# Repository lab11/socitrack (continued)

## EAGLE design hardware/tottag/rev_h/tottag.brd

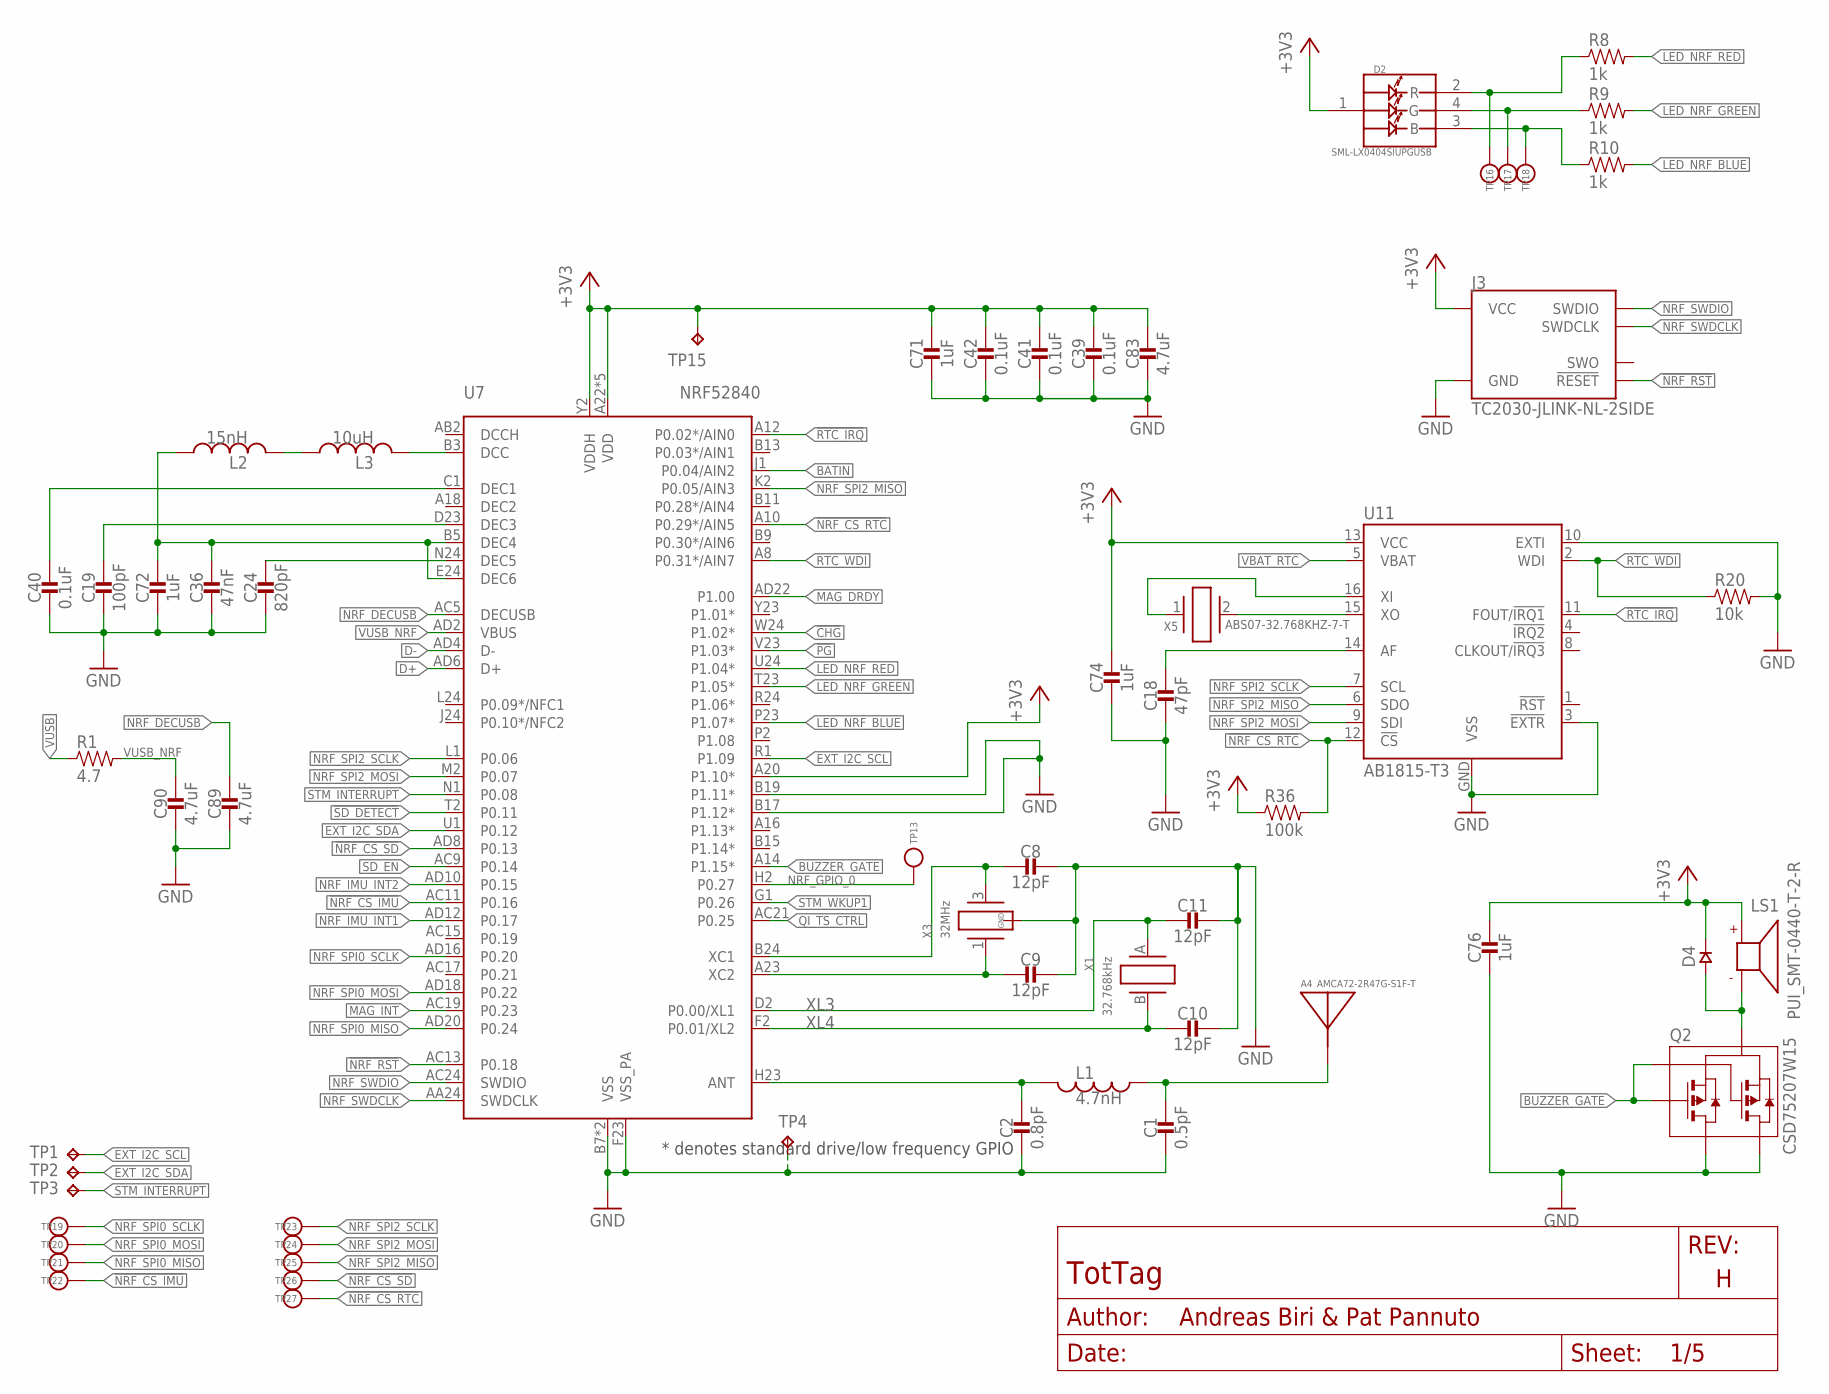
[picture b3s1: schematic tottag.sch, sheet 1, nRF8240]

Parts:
A4: AMCA72-2R47G-S1F-T; AMCA72-2R470G-S1F-T
C1: 0.5pF; 0402_CAP; MPN GJM1555C1HR50WB01D; DIGIKEY 490-11250-1-ND
C2: 0.8pF; 0402_CAP; MPN GJM1555C1HR80WB01D; DIGIKEY 490-11253-1-ND
C8, C9, C10, C11: 12pF; 0402_CAP; MPN CBR04C120F5GAC; DIGIKEY 399-8815-2-ND
C18: 47pF; 0402_CAP; MPN GRM1555C1H470JA01D; DIGIKEY 490-5942-1-ND
C19: 100pF; 0402_CAP; MPN GRM1555C1H101JA01D; DIGIKEY 490-5922-1-ND
C24: 820pF; 0402_CAP; MPN C0402C821J5GACTU; DIGIKEY 399-11129-2-ND
C36: 47nF; 0402_CAP; MPN C1005X7R1C473K050BC; DIGIKEY 445-1264-1-ND
C39, C40, C41: 0.1uF; 0402_CAP; MPN GRM155R71C104KA88J; DIGIKEY 490-6328-1-ND
C42: 0.1uF; 0402_CAP
C71: 1uF; 0402_CAP
C72, C74, C76: 1uF; 0402_CAP; MPN GRM155R70G105KA12D; DIGIKEY 490-7195-1-ND
C83: 4.7uF; 0402_CAP
C89, C90: 4.7uF; 0402_CAP; MPN C1005X5R0J475K050BC; DIGIKEY 445-5947-1-ND
D2: SML-LX0404SIUPGUSB; 1MM_SQ_4PAD
D4: DIODE0402; 0402_DIODE; MPN CDSQR400B-HF; DIGIKEY 641-2087-1-ND
J3: TC2030-JLINK-NL-2SIDE; TC2030-IDC-NL-2SIDE
L1: 4.7nH; 0402_CAP; MPN LQW15AN4N7G8ZD; DIGIKEY 490-15482-1-ND
L2: 15nH; 0402_CAP; MPN HK100515NJ-T; DIGIKEY 587-1521-1-ND
L3: 10uH; 0603_CAP; MPN LQM18FN100M00D; DIGIKEY 490-4025-1-ND
LS1: PUI_SMT-0440-T-2-R; SMT-0440-T-2-R
Q2: CSD75207W15; DSBGA
R1: 4.7; 0402_RES; MPN RMCF0402FT4R70; DIGIKEY RMCF0402FT4R70CT-ND
R8: 1k; 0402_RES; MPN RMCF0402FT1K00; DIGIKEY RMCF0402FT1K00CT-ND
R9, R10: 1k; 0402_RES
R20: 10k; 0402_RES; MPN RC0402JR-0710KL; DIGIKEY 311-10KJRCT-ND
R36: 100k; 0402_RES
TP1, TP2, TP3, TP4, TP15: TPTP06SQ; TP06SQ
TP13, TP16, TP17, TP18, TP19, TP20, TP21, TP22, TP23, TP24, TP25, TP26, TP27: TEST-POINT; PAD.03X.03
U7: NRF52840; AQFN73
U11: AB1815-T3; QFN-16-3MM
X1: 32.768kHz; ABS05
X3: 32MHz; TXC-7V
X5: ABS07-32.768KHZ-7-T; ABS07

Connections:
!CHG: U7.W24 (P1.02*); also elsewhere on the board
!NRF_CS_IMU: TP22.P$1, U7.AC11 (P0.16); also elsewhere on the board
!NRF_CS_RTC: R36.2, TP27.P$1, U7.A10 (P0.29*/AIN5), U11.12 (!CS)
!NRF_CS_SD: TP26.P$1, U7.AD8 (P0.13); also elsewhere on the board
!NRF_RST: J3.3 (!RESET), J3.B3 (!RESET), U7.AC13 (P0.18)
!PG: U7.V23 (P1.03*); also elsewhere on the board
!RTC_IRQ: U7.A12 (P0.02*/AIN0), U11.11 (FOUT/!IRQ1)
!SD_DETECT: U7.T2 (P0.11); also elsewhere on the board
+3V3: C39.1, C41.1, C42.1, C71.1, C74.1, C76.1, C83.1, D2.1 (VDD), D4.CATHODE, J3.1 (VCC), J3.B1 (VCC), LS1.+, R36.1, TP15.TP, U7.A20 (P1.10*), U7.A22 (VDD), U7.AD14 (VDD), U7.AD23 (VDD), U7.B1 (VDD), U7.W1 (VDD), U7.Y2 (VDDH), U11.13 (VCC); also elsewhere on the board
BATIN: U7.J1 (P0.04/AIN2); also elsewhere on the board
BLE_ANT: A4.S1, C1.1, L1.1
BUZZER_GATE: Q2.A1 (G1), Q2.C1 (G2), U7.A14 (P1.15*)
D+: U7.AD6 (D+); also elsewhere on the board
D-: U7.AD4 (D-); also elsewhere on the board
EXT_I2C_SCL: TP1.TP, U7.R1 (P1.09); also elsewhere on the board
EXT_I2C_SDA: TP2.TP, U7.U1 (P0.12); also elsewhere on the board
GND: C1.2, C2.2, C8.1, C9.1, C10.1, C11.1, C18.2, C19.2, C24.2, C36.2, C39.2, C40.2, C41.2, C42.2, C71.2, C72.2, C74.2, C76.2, C83.2, C89.2, C90.2, J3.5 (GND), J3.B5 (GND), Q2.A2 (D1), Q2.A3 (D1), Q2.B2 (D2), Q2.B3 (D1), Q2.C2 (D2), Q2.C3 (D2), R20.2, TP4.TP, U7.B7 (VSS), U7.B17 (P1.12*), U7.B19 (P1.11*), U7.F23 (VSS_PA), U7.GND (VSS), U11.3 (!EXTR), U11.10 (EXTI), U11.GND (VSS), X3.2 (GND), X3.4 (GND); also elsewhere on the board
LED_NRF_BLUE: R10.2, U7.P23 (P1.07*)
LED_NRF_BLUE_COMM: D2.3 (B), R10.1, TP18.P$1
LED_NRF_GREEN: R9.2, U7.T23 (P1.05*)
LED_NRF_GREEN_COMM: D2.4 (G), R9.1, TP17.P$1
LED_NRF_RED: R8.2, U7.U24 (P1.04*)
LED_NRF_RED_COMM: D2.2 (R), R8.1, TP16.P$1
MAG_DRDY: U7.AD22 (P1.00); also elsewhere on the board
MAG_INT: U7.AC19 (P0.23); also elsewhere on the board
unnamed: D4.ANODE, LS1.- (N), Q2.B1 (S)
unnamed: C2.1, L1.2, U7.H23 (ANT)
unnamed: C8.2, U7.B24 (XC1), X3.3 (2)
unnamed: C9.2, U7.A23 (XC2), X3.1
unnamed: C18.1, U11.14 (AF)
unnamed: L2.2, L3.1
unnamed: U11.16 (XI), X5.1
unnamed: U11.15 (XO), X5.2
NRF_DCC: L3.2, U7.B3 (DCC)
NRF_DECAP1: C40.1, U7.C1 (DEC1)
NRF_DECAP3: C19.1, U7.D23 (DEC3)
NRF_DECAP5: C24.1, U7.N24 (DEC5)
NRF_DECAP46: C36.1, C72.1, L2.1, U7.B5 (DEC4), U7.E24 (DEC6)
NRF_DECUSB: C89.1, U7.AC5 (DECUSB)
NRF_GPIO_0: TP13.P$1, U7.H2 (P0.27)
NRF_IMU_INT1: U7.AD12 (P0.17); also elsewhere on the board
NRF_IMU_INT2: U7.AD10 (P0.15); also elsewhere on the board
NRF_SPI0_MISO: TP21.P$1, U7.AD20 (P0.24); also elsewhere on the board
NRF_SPI0_MOSI: TP20.P$1, U7.AD18 (P0.22); also elsewhere on the board
NRF_SPI0_SCLK: TP19.P$1, U7.AD16 (P0.20); also elsewhere on the board
NRF_SPI2_MISO: TP25.P$1, U7.K2 (P0.05/AIN3), U11.6 (SDO); also elsewhere on the board
NRF_SPI2_MOSI: TP24.P$1, U7.M2 (P0.07), U11.9 (SDI); also elsewhere on the board
NRF_SPI2_SCLK: TP23.P$1, U7.L1 (P0.06), U11.7 (SCL); also elsewhere on the board
NRF_SWDCLK: J3.4 (SWDCLK), J3.B4 (SWDCLK), U7.AA24 (SWDCLK)
NRF_SWDIO: J3.2 (SWDIO), J3.B2 (SWDIO), U7.AC24 (SWDIO)
QI_TS_CTRL: U7.AC21 (P0.25); also elsewhere on the board
RTC_WDI: R20.1, U7.A8 (P0.31*/AIN7), U11.2 (WDI)
SD_EN: U7.AC9 (P0.14); also elsewhere on the board
STM_INTERRUPT: TP3.TP, U7.N1 (P0.08); also elsewhere on the board
STM_WKUP1: U7.G1 (P0.26); also elsewhere on the board
VBAT_RTC: U11.5 (VBAT); also elsewhere on the board
VUSB: R1.1; also elsewhere on the board
VUSB_NRF: C90.1, R1.2, U7.AD2 (VBUS)
XL3: C11.2, U7.D2 (P0.00/XL1), X1.A (1)
XL4: C10.2, U7.F2 (P0.01/XL2), X1.B (2)

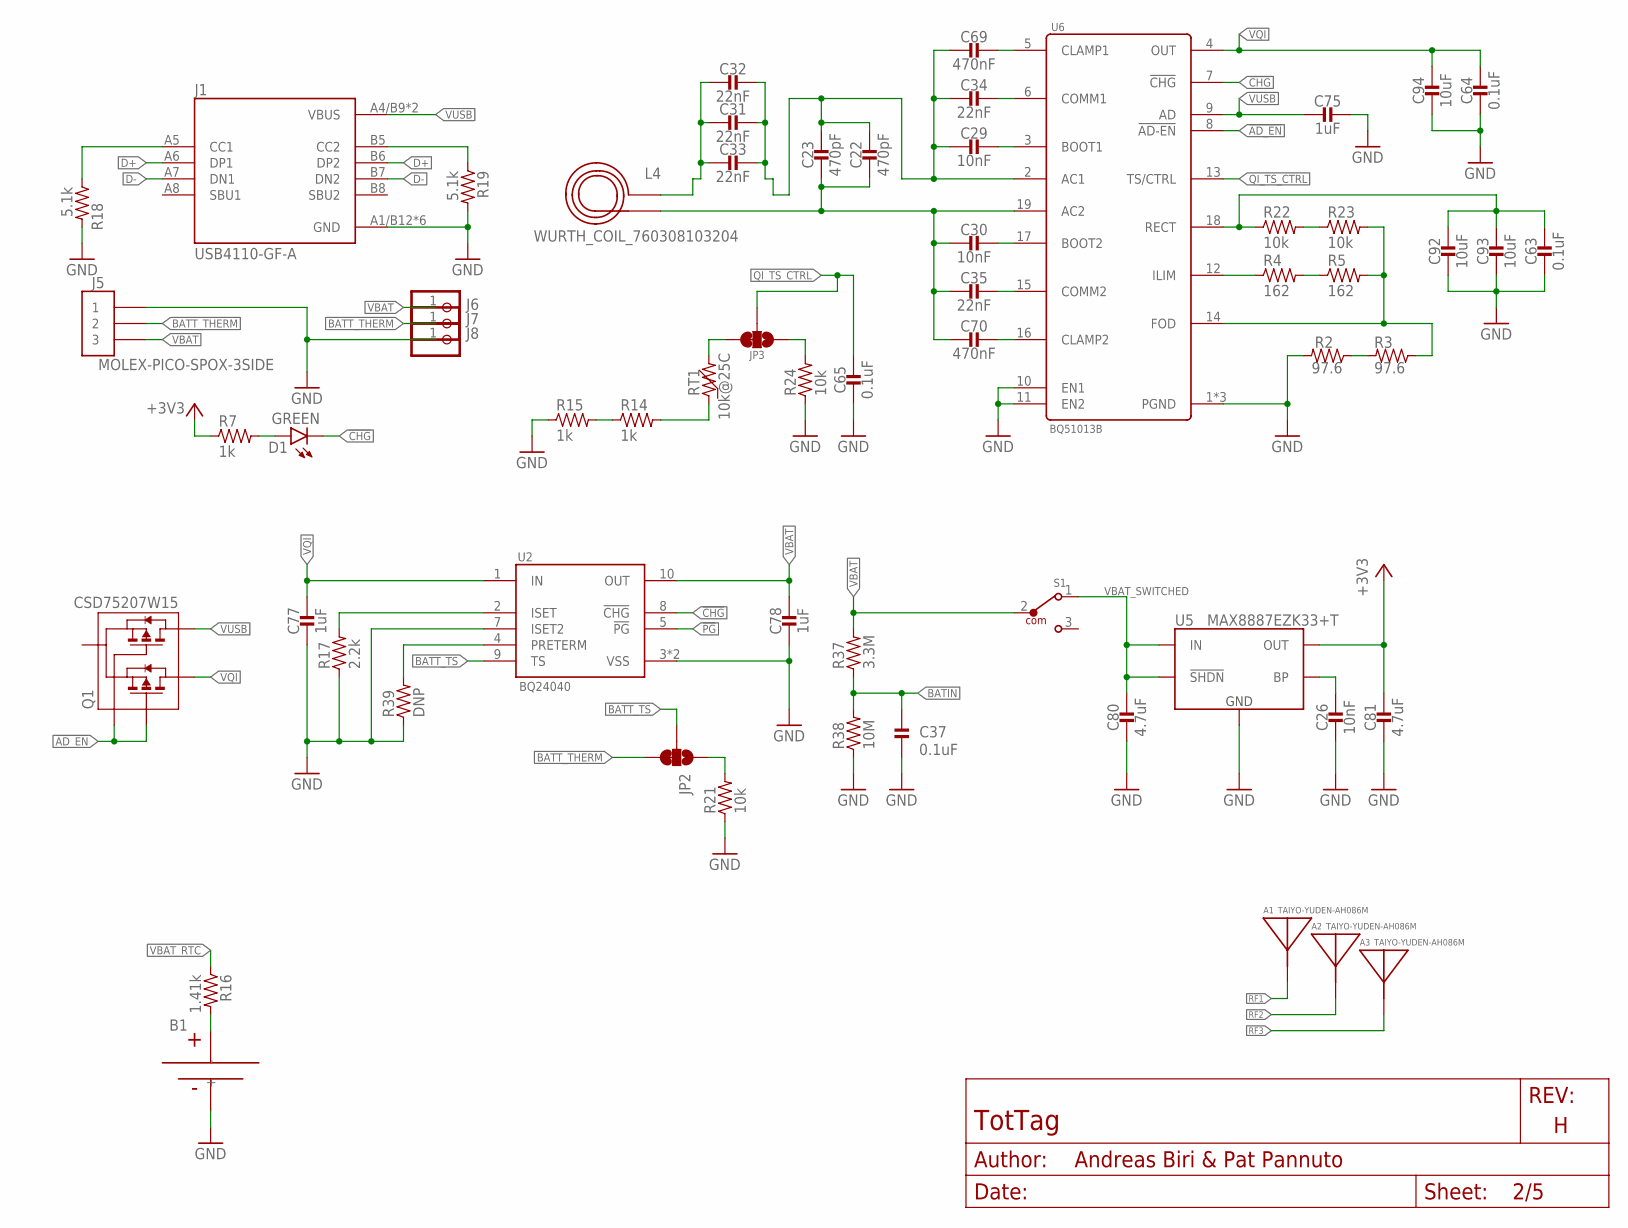
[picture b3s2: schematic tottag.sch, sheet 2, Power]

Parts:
A1, A2, A3: TAIYO-YUDEN-AH086M
B1: MS518SE; MS518SE-FL35E
C22, C23: 470pF; 0402_CAP; MPN GRM1555C1H471JA01J; DIGIKEY 490-6242-1-ND
C26: 10nF; 0402_CAP
C29, C30: 10nF; 0402_CAP; MPN GRM155R71H103KA88J; DIGIKEY 490-6351-2-ND
C31, C32, C33: 22nF; 0402_CAP; MPN GRM155R71E223JA61D; DIGIKEY 490-10699-2-ND
C34, C35: 22nF; 0402_CAP; MPN CC0402ZRY5V8BB223; DIGIKEY 311-3823-1-ND
C37: 0.1uF; 0402_CAP
C63, C64, C65: 0.1uF; 0402_CAP; MPN GRM155R71C104KA88J; DIGIKEY 490-6328-1-ND
C69, C70: 470nF; 0402_CAP; MPN GRT155R61E474ME01D; DIGIKEY 490-12270-1-ND
C75: 1uF; 0402_CAP
C77, C78: 1uF; 0402_CAP; MPN GRM155R70G105KA12D; DIGIKEY 490-7195-1-ND
C80, C81: 4.7uF; 0402_CAP
C92, C93, C94: 10uF; 0603_CAP; MPN CM105X5R106M25AT; DIGIKEY 1253-CM105X5R106M25ATCT-ND
D1: GREEN; LED-0603; MPN LTST-C191KGKT; DIGIKEY 160-1446-1-ND
J1: USB4110-GF-A; GCT_USB4110-GF-A
J5: MOLEX-PICO-SPOX-3SIDE; MOLEX-PICO-SPOX-3_SIDE
J6, J7, J8: PINHD-1X1; 1X01
JP2, JP3: JUMPER-SMT_3_1-NC_TRACE_SILK; SMT-JUMPER_3_1-NC_TRACE_SILK
L4: WURTH_COIL_760308103204
Q1: CSD75207W15; DSBGA
R2, R3: 97.6; 0402_RES; MPN RMCF0402FT97R6; DIGIKEY RMCF0402FT97R6CT-ND
R4, R5: 162; 0402_RES; MPN RMCF0402FT162R; DIGIKEY RMCF0402FT162RCT-ND
R7, R14, R15: 1k; 0402_RES
R16: 1.41k; 0402_RES; MPN RMCF0402FT1K40; DIGIKEY RMCF0402FT1K40CT-ND
R17: 2.2k; 0402_RES; MPN RMCF0402JT2K20; DIGIKEY RMCF0402JT2K20CT-ND
R18, R19: 5.1k; 0402_RES; MPN RMCF0402FT5K10; DIGIKEY RMCF0402FT5K10CT-ND
R21, R22, R23, R24: 10k; 0402_RES; MPN RC0402JR-0710KL; DIGIKEY 311-10KJRCT-ND
R37: 3.3M; 0402_RES; MPN RMCF0402FT3M30; DIGIKEY RMCF0402FT3M30CT-ND
R38: 10M; 0402_RES; MPN RMCF0402FT10M0; DIGIKEY RMCF0402FT10M0CT-ND
R39: DNP; 0402_RES
RT1: 10k@25C; 0402_RES; MPN NCU15XH103F60RC; DIGIKEY 490-18149-1-ND
S1: 450404015514; DIGIKEY 732-13665-1-ND
U2: BQ24040; DSQ0010A
U5: MAX8887EZK33+T; SOT-23-5
U6: BQ51013B; RHL0020A

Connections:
!AD_EN: Q1.A1 (G1), Q1.C1 (G2), U6.8 (!AD-EN)
!CHG: D1.C, U2.8 (!CHG), U6.7 (!CHG); also elsewhere on the board
!PG: U2.5 (!PG); also elsewhere on the board
+3V3: C81.1, R7.1, U5.5 (OUT); also elsewhere on the board
BATIN: C37.2, R37.1, R38.2; also elsewhere on the board
BATT_THERM: J5.2, J5.2SUPP (2), J7.1, JP2.3
BATT_TS: JP2.2, U2.9 (TS)
BQ_AC1: C22.1, C23.1, C29.2, C31.1, C32.1, C33.1, C34.2, C69.2, U6.2 (AC1)
BQ_AC2: C22.2, C23.2, C30.2, C35.2, C70.2, L4.P$2 (2), U6.19 (AC2)
BQ_BOOT1: C29.1, U6.3 (BOOT1)
BQ_BOOT2: C30.1, U6.17 (BOOT2)
BQ_CLAMP1: C69.1, U6.5 (CLAMP1)
BQ_CLAMP2: C70.1, U6.16 (CLAMP2)
BQ_COMM1: C34.1, U6.6 (COMM1)
BQ_COMM2: C35.1, U6.15 (COMM2)
BQ_FOD: R3.1, R5.2, R23.2, U6.14 (FOD)
BQ_ILM: R4.1, U6.12 (ILIM)
BQ_RECT: C63.1, C92.1, C93.1, R22.1, U6.18 (RECT)
COIL_AC1: C31.2, C32.2, C33.2, L4.P$1 (1)
D+: J1.A6 (DP1), J1.B6 (DP2); also elsewhere on the board
D-: J1.A7 (DN1), J1.B7 (DN2); also elsewhere on the board
GND: B1.-, C26.2, C37.1, C63.2, C64.2, C65.2, C75.1, C77.2, C78.2, C80.2, C81.2, C92.2, C93.2, C94.2, J1.A1/B12 (GND), J1.B1/A12 (GND), J1.S1 (GND), J1.S2 (GND), J1.S3 (GND), J1.S4 (GND), J5.1, J5.1SUPP (1), J8.1, R2.2, R15.1, R17.1, R18.2, R19.2, R21.1, R24.1, R38.1, R39.1, U2.3 (VSS), U2.7 (ISET2), U2.PAD (VSS), U5.2 (GND), U6.1 (PGND), U6.10 (EN1), U6.11 (EN2), U6.20 (PGND), U6.PAD (PGND); also elsewhere on the board
unnamed: J1.B5 (CC2), R19.1
unnamed: C26.1, U5.4 (BP)
unnamed: J1.A5 (CC1), R18.1
unnamed: R2.1, R3.2
unnamed: R17.2, U2.2 (ISET)
unnamed: B1.+, R16.2
unnamed: JP2.1, R21.2
unnamed: R39.2, U2.4 (PRETERM)
unnamed: D1.A, R7.2
unnamed: R22.2, R23.1
unnamed: R4.2, R5.1
unnamed: JP3.1, R24.2
unnamed: JP3.3, RT1.2
unnamed: R14.2, RT1.1
unnamed: R14.1, R15.2
QI_TS_CTRL: C65.1, JP3.2, U6.13 (TS/CTRL); also elsewhere on the board
RF1: A1.A; also elsewhere on the board
RF2: A2.A; also elsewhere on the board
RF3: A3.A; also elsewhere on the board
VBAT: C78.1, J5.3, J5.3SUPP (3), J6.1, R37.2, S1.2, U2.10 (OUT)
VBAT_RTC: R16.1; also elsewhere on the board
VBAT_SWITCHED: C80.1, S1.1, U5.1 (IN), U5.3 (!SHDN)
VQI: C64.1, C77.1, C94.1, Q1.A2 (D1), Q1.A3 (D1), Q1.B3 (D1), U2.1 (IN), U6.4 (OUT)
VUSB: C75.2, J1.A4/B9 (VBUS), J1.B4/A9 (VBUS), Q1.B2 (D2), Q1.C2 (D2), Q1.C3 (D2), U6.9 (AD); also elsewhere on the board

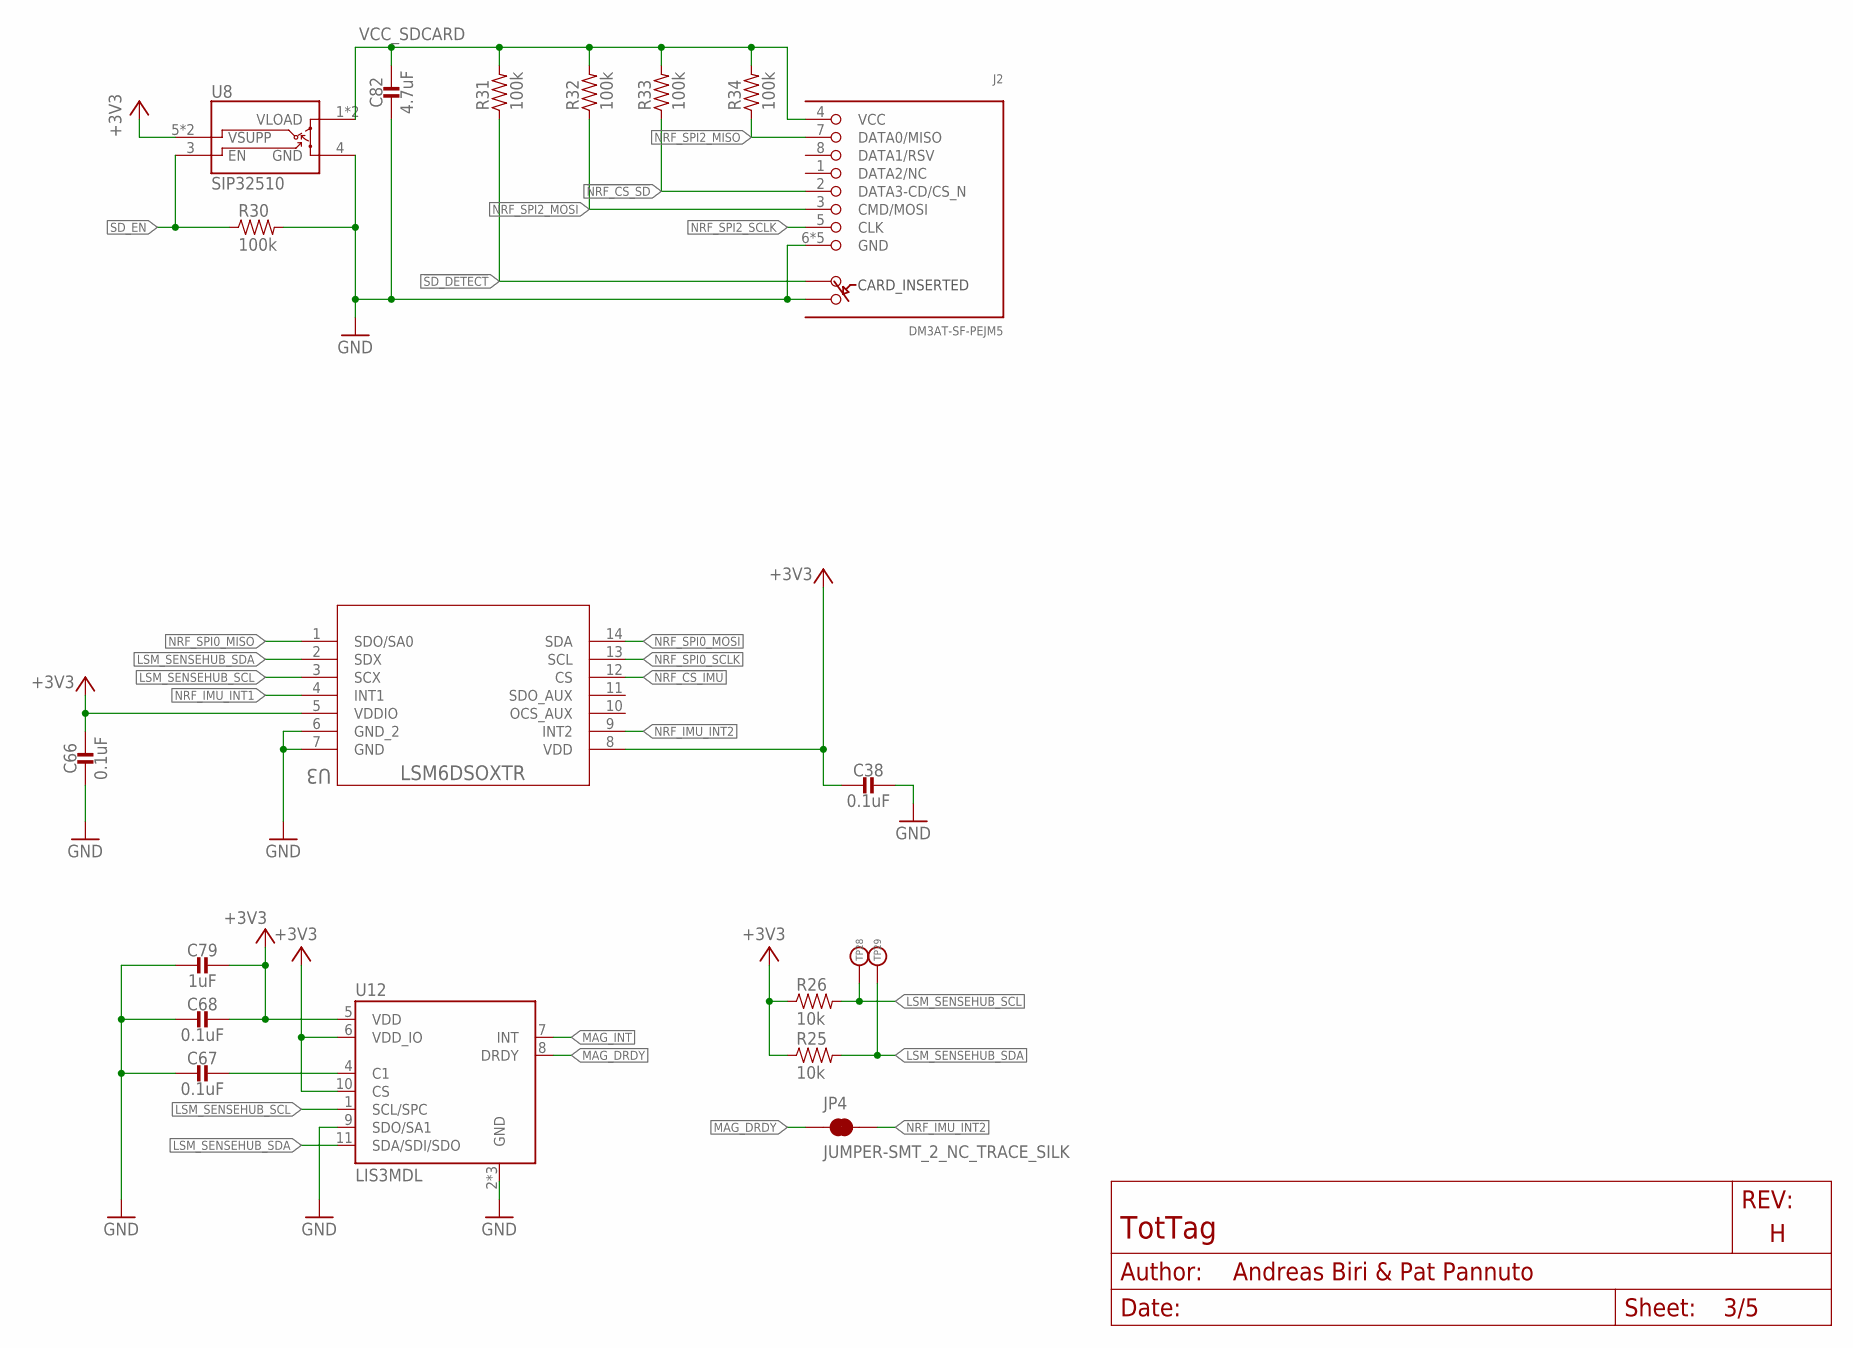
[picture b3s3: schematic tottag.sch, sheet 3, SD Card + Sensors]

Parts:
C38, C66, C67, C68: 0.1uF; 0402_CAP; MPN GRM155R71C104KA88J; DIGIKEY 490-6328-1-ND
C79: 1uF; 0402_CAP; MPN GRM155R70G105KA12D; DIGIKEY 490-7195-1-ND
C82: 4.7uF; 0402_CAP; MPN C1005X5R0J475K050BC; DIGIKEY 445-5947-1-ND
J2: DM3AT-SF-PEJM5
JP4: JUMPER-SMT_2_NC_TRACE_SILK; SMT-JUMPER_2_NC_TRACE_SILK
R25, R26: 10k; 0402_RES; MPN RC0402JR-0710KL; DIGIKEY 311-10KJRCT-ND
R30, R31, R32, R33, R34: 100k; 0402_RES
TP28, TP29: TEST-POINT; PAD.03X.03
U3: LSM6DSOXTR; LGA-14L_STM
U8: SIP32510; TSOT23-6
U12: LIS3MDL; LGA-12

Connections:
!NRF_CS_IMU: U3.12 (CS); also elsewhere on the board
!NRF_CS_SD: J2.2 (DATA3-CD/CS_N), R33.1; also elsewhere on the board
!SD_DETECT: J2.A, R31.1; also elsewhere on the board
+3V3: C38.2, C66.1, C68.1, C79.1, R25.1, R26.1, U3.5 (VDDIO), U3.8 (VDD), U8.5 (VSUPP), U8.6 (VSUPP), U12.5 (VDD), U12.6 (VDD_IO), U12.10 (CS); also elsewhere on the board
GND: C38.1, C66.2, C67.2, C68.2, C79.2, C82.2, J2.6 (GND), J2.B, J2.MOUNT0 (GND), J2.MOUNT1 (GND), J2.MOUNT2 (GND), J2.MOUNT3 (GND), R30.2, U3.6 (GND_2), U3.7 (GND), U8.4 (GND), U12.2 (GND), U12.3 (GND), U12.9 (SDO/SA1), U12.12 (GND); also elsewhere on the board
LSM_SENSEHUB_SCL: R26.2, TP28.P$1, U3.3 (SCX), U12.1 (SCL/SPC)
LSM_SENSEHUB_SDA: R25.2, TP29.P$1, U3.2 (SDX), U12.11 (SDA/SDI/SDO)
MAG_DRDY: JP4.1, U12.8 (DRDY); also elsewhere on the board
MAG_INT: U12.7 (INT); also elsewhere on the board
unnamed: C67.1, U12.4 (C1)
NRF_IMU_INT1: U3.4 (INT1); also elsewhere on the board
NRF_IMU_INT2: JP4.2, U3.9 (INT2); also elsewhere on the board
NRF_SPI0_MISO: U3.1 (SDO/SA0); also elsewhere on the board
NRF_SPI0_MOSI: U3.14 (SDA); also elsewhere on the board
NRF_SPI0_SCLK: U3.13 (SCL); also elsewhere on the board
NRF_SPI2_MISO: J2.7 (DATA0/MISO), R34.1; also elsewhere on the board
NRF_SPI2_MOSI: J2.3 (CMD/MOSI), R32.1; also elsewhere on the board
NRF_SPI2_SCLK: J2.5 (CLK); also elsewhere on the board
SD_EN: R30.1, U8.3 (EN); also elsewhere on the board
VCC_SDCARD: C82.1, J2.4 (VCC), R31.2, R32.2, R33.2, R34.2, U8.1 (VLOAD), U8.2 (VLOAD)

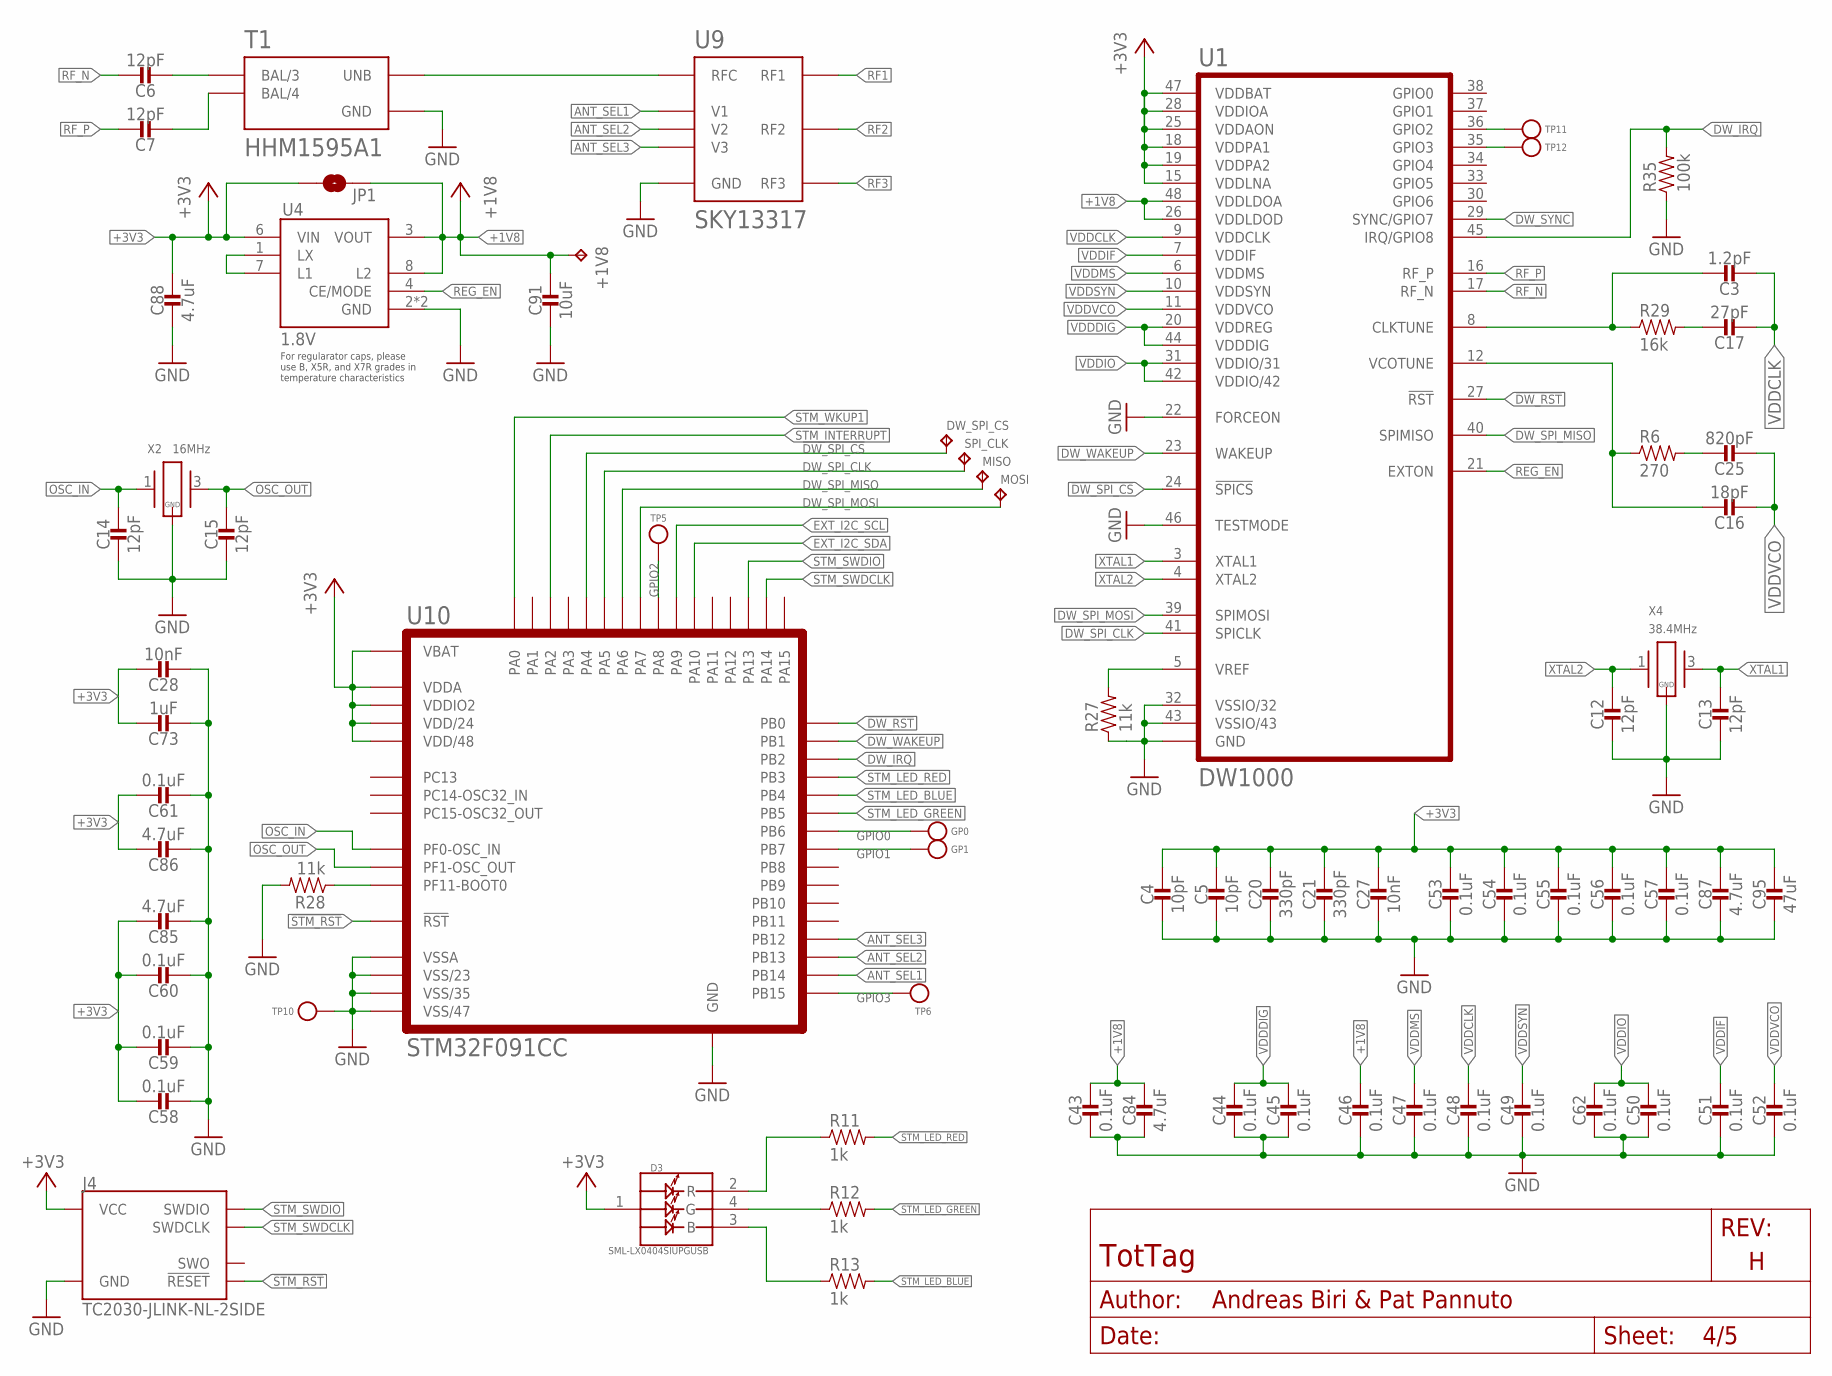
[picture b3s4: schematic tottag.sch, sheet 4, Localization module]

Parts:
+1V8: TPTP06SQ; TP06SQ
C3: 1.2pF; 0402_CAP; MPN GJM1555C1H1R2CB01D; DIGIKEY 490-3085-1-ND
C4, C5: 10pF; 0402_CAP; MPN 885012005074; DIGIKEY 732-12054-1-ND
C6, C7: 12pF; 0201_CAP; MPN CBR02C120F3GAC; DIGIKEY 399-8604-2-ND
C12, C13, C14, C15: 12pF; 0402_CAP; MPN CBR04C120F5GAC; DIGIKEY 399-8815-2-ND
C16: 18pF; 0402_CAP; MPN CBR04C180F5GAC; DIGIKEY 399-8828-1-ND
C17: 27pF; 0402_CAP; MPN GJM1555C1H270FB01D; DIGIKEY 490-16380-1-ND
C20, C21: 330pF; 0402_CAP; MPN CC0402JRX7R9BB331; DIGIKEY 311-3768-1-ND
C25: 820pF; 0402_CAP; MPN C0402C821J5GACTU; DIGIKEY 399-11129-2-ND
C27, C28: 10nF; 0402_CAP
C43, C44, C45, C46, C47, C48, C49, C50, C51, C52, C53, C54, C55, C56, C57, C58, C59, C60, C61, C62: 0.1uF; 0402_CAP
C73: 1uF; 0402_CAP
C84, C85, C86, C87, C88: 4.7uF; 0402_CAP
C91: 10uF; 0603_CAP; MPN CM105X5R106M25AT; DIGIKEY 1253-CM105X5R106M25ATCT-ND
C95: 47uF; 0603_CAP; MPN GRM188R60J476ME15D; DIGIKEY 490-13247-1-ND
D3: SML-LX0404SIUPGUSB; 1MM_SQ_4PAD
DW_SPI_CS: TPTP06SQ; TP06SQ
GP0, GP1: TEST-POINT; PAD.03X.03
J4: TC2030-JLINK-NL-2SIDE; TC2030-IDC-NL-2SIDE
JP1: JUMPER-SMT_2_NO_SILK; SMT-JUMPER_2_NO_SILK
MISO: TPTP06SQ; TP06SQ
MOSI: TPTP06SQ; TP06SQ
R6: 270; 0402_RES; MPN RMCF0402FT270R; DIGIKEY RMCF0402FT270RCT-ND
R11, R12, R13: 1k; 0402_RES
R27, R28: 11k; 0402_RES; MPN RMCF0402FT11K0; DIGIKEY RMCF0402FT11K0CT-ND
R29: 16k; 0402_RES; MPN RMCF0402FT16K0; DIGIKEY RMCF0402FT16K0CT-ND
R35: 100k; 0402_RES
SPI_CLK: TPTP06SQ; TP06SQ
T1: HHM1595A1; EIA-0805
TP5, TP6, TP10, TP11, TP12: TEST-POINT; PAD.03X.03
U1: DW1000; QFN-48-DW1000
U4: 1.8V; XCL20X
U9: SKY13317; MLPQ-UT-8
U10: STM32F091CC; UFQFPN-48
X2: 16MHz; FA-20H; MPN FA-20H 16.0000MF10Z-AJ3; DIGIKEY SER3913CT-ND
X4: 38.4MHz; FA-20H; MPN FA-20H 38.4000MF10Z-AS3; DIGIKEY SER3631CT-ND

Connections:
!DW_RST: U1.27 (!RST), U10.18 (PB0)
!DW_SPI_CS: DW_SPI_CS.TP, U1.24 (!SPICS), U10.14 (PA4)
!STM_RST: J4.3 (!RESET), J4.B3 (!RESET), U10.7 (!RST)
+1V8: +1V8.TP, C43.1, C46.1, C84.1, C91.1, JP1.2, U1.26 (VDDLDOD), U1.48 (VDDLDOA), U4.3 (VOUT), U4.8 (L2)
+3V3: C4.1, C5.1, C20.1, C21.1, C27.1, C28.1, C53.1, C54.1, C55.1, C56.1, C57.1, C58.1, C59.1, C60.1, C61.1, C73.1, C85.1, C86.1, C87.1, C88.1, C95.1, D3.1 (VDD), J4.1 (VCC), J4.B1 (VCC), JP1.1, U1.15 (VDDLNA), U1.18 (VDDPA1), U1.19 (VDDPA2), U1.25 (VDDAON), U1.28 (VDDIOA), U1.47 (VDDBAT), U4.6 (VIN), U10.1 (VBAT), U10.9 (VDDA), U10.24 (VDD/24), U10.36 (VDDIO2), U10.48 (VDD/48); also elsewhere on the board
ANT_SEL1: U9.3 (V1), U10.27 (PB14)
ANT_SEL2: U9.6 (V2), U10.26 (PB13)
ANT_SEL3: U9.7 (V3), U10.25 (PB12)
DW_IRQ: R35.2, U1.45 (IRQ/GPIO8), U10.20 (PB2)
DW_SPI_CLK: SPI_CLK.TP, U1.41 (SPICLK), U10.15 (PA5)
DW_SPI_MISO: MISO.TP, U1.40 (SPIMISO), U10.16 (PA6)
DW_SPI_MOSI: MOSI.TP, U1.39 (SPIMOSI), U10.17 (PA7)
DW_SYNC: U1.29 (SYNC/GPIO7)
DW_WAKEUP: U1.23 (WAKEUP), U10.19 (PB1)
EXT_I2C_SCL: U10.30 (PA9); also elsewhere on the board
EXT_I2C_SDA: U10.31 (PA10); also elsewhere on the board
GND: C4.2, C5.2, C12.2, C13.2, C14.2, C15.2, C20.2, C21.2, C27.2, C28.2, C43.2, C44.2, C45.2, C46.2, C47.2, C48.2, C49.2, C50.2, C51.2, C52.2, C53.2, C54.2, C55.2, C56.2, C57.2, C58.2, C59.2, C60.2, C61.2, C62.2, C73.2, C84.2, C85.2, C86.2, C87.2, C88.2, C91.2, C95.2, J4.5 (GND), J4.B5 (GND), R27.1, R28.2, R35.1, T1.2 (GND), T1.5 (GND), TP10.P$1, U1.22 (FORCEON), U1.32 (VSSIO/32), U1.43 (VSSIO/43), U1.46 (TESTMODE), U1.GND, U4.2 (GND), U4.5 (GND), U9.GND, U10.8 (VSSA), U10.23 (VSS/23), U10.35 (VSS/35), U10.47 (VSS/47), U10.GND, X2.2 (GND), X2.4 (GND), X4.2 (GND), X4.4 (GND); also elsewhere on the board
GPIO0: GP0.P$1, U10.42 (PB6)
GPIO1: GP1.P$1, U10.43 (PB7)
GPIO2: TP5.P$1, U10.29 (PA8)
GPIO3: TP6.P$1, U10.28 (PB15)
unnamed: T1.1 (UNB), U9.1 (RFC)
unnamed: C6.P$2 (2), T1.3 (BAL/3)
unnamed: C7.P$2 (2), T1.4 (BAL/4)
unnamed: C25.1, R6.2
unnamed: C17.1, R29.2
unnamed: C16.1, R6.1, U1.12 (VCOTUNE)
unnamed: C3.1, R29.1, U1.8 (CLKTUNE)
unnamed: R27.2, U1.5 (VREF)
unnamed: R28.1, U10.44 (PF11-BOOT0)
unnamed: TP11.P$1, U1.36 (GPIO2)
unnamed: TP12.P$1, U1.35 (GPIO3)
unnamed: U4.1 (LX), U4.7 (L1)
OSC_IN: C14.1, U10.5 (PF0-OSC_IN), X2.1
OSC_OUT: C15.1, U10.6 (PF1-OSC_OUT), X2.3 (2)
REG_EN: U1.21 (EXTON), U4.4 (CE/MODE)
RF1: U9.4 (RF1); also elsewhere on the board
RF2: U9.5 (RF2); also elsewhere on the board
RF3: U9.8 (RF3); also elsewhere on the board
RF_N: C6.P$1 (1), U1.17 (RF_N)
RF_P: C7.P$1 (1), U1.16 (RF_P)
STM_INTERRUPT: U10.12 (PA2); also elsewhere on the board
STM_LED_BLUE: R13.2, U10.40 (PB4)
STM_LED_BLUE_COMM: D3.3 (B), R13.1
STM_LED_GREEN: R12.2, U10.41 (PB5)
STM_LED_GREEN_COMM: D3.4 (G), R12.1
STM_LED_RED: R11.2, U10.39 (PB3)
STM_LED_RED_COMM: D3.2 (R), R11.1
STM_SWDCLK: J4.4 (SWDCLK), J4.B4 (SWDCLK), U10.37 (PA14)
STM_SWDIO: J4.2 (SWDIO), J4.B2 (SWDIO), U10.34 (PA13)
STM_WKUP1: U10.10 (PA0); also elsewhere on the board
VDDCLK: C3.2, C17.2, C48.1, U1.9 (VDDCLK)
VDDDIG: C44.1, C45.1, U1.20 (VDDREG), U1.44 (VDDDIG)
VDDIF: C51.1, U1.7 (VDDIF)
VDDIO: C50.1, C62.1, U1.31 (VDDIO/31), U1.42 (VDDIO/42)
VDDMS: C47.1, U1.6 (VDDMS)
VDDSYN: C49.1, U1.10 (VDDSYN)
VDDVCO: C16.2, C25.2, C52.1, U1.11 (VDDVCO)
XTAL1: C13.1, U1.3 (XTAL1), X4.3 (2)
XTAL2: C12.1, U1.4 (XTAL2), X4.1

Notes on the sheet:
For regularator caps, please use B, X5R, and X7R grades in temperature characteristics
